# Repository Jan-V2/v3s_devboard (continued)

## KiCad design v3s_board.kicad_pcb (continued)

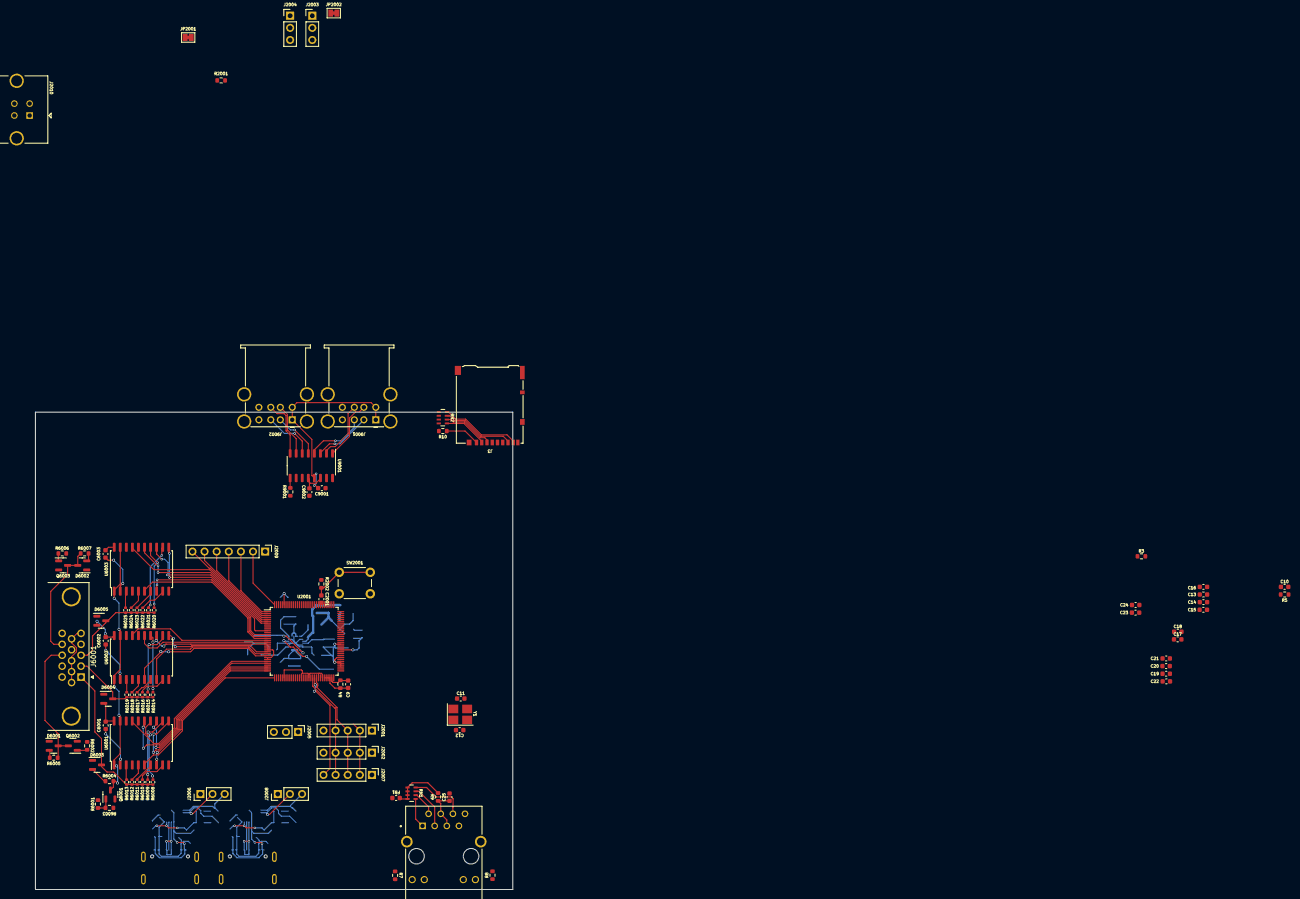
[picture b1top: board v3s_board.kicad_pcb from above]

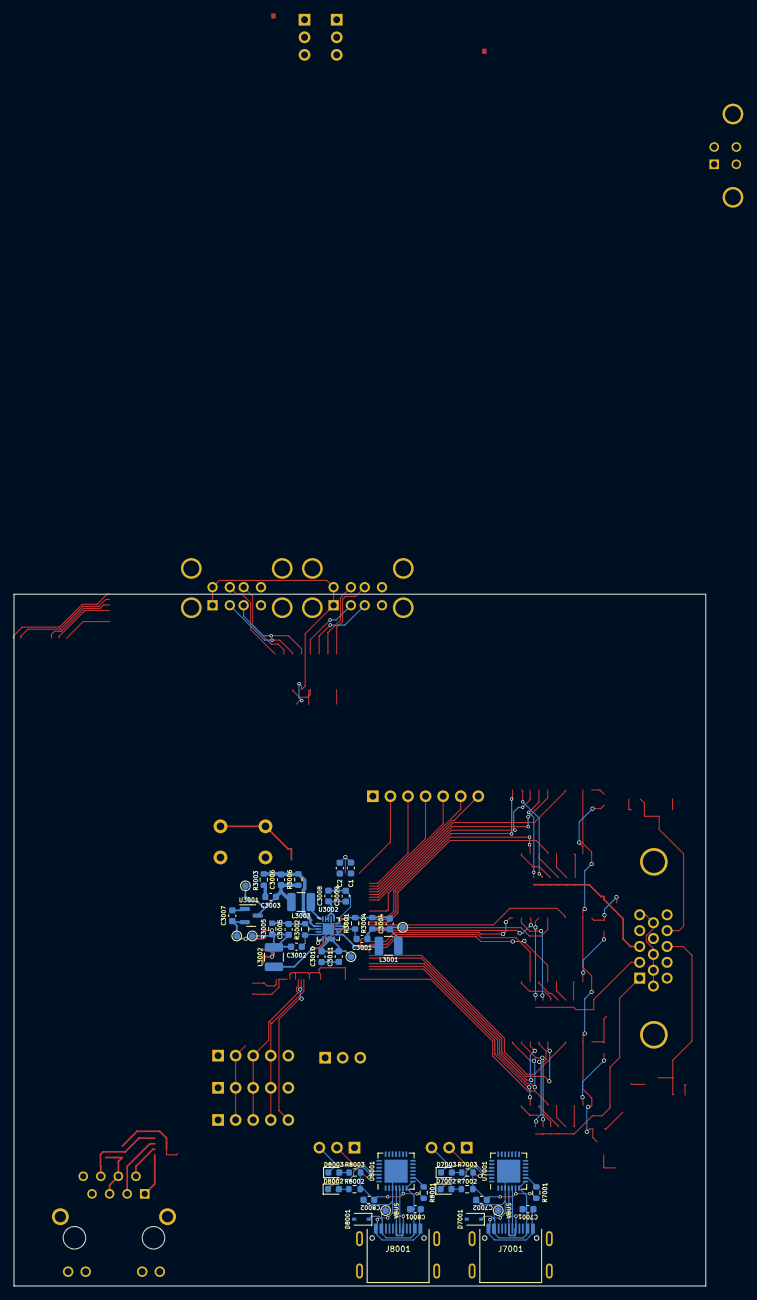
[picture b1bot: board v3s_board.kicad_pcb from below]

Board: 4 copper layers, 100.0 x 100.0 mm, 144 parts (51 on the bottom side), 134 nets.

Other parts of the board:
C7001, C7002: 100nf; C_0603_1608Metric
D7001: SD05_SOD323; D_SOD-323
D7002: LED YEL; LED_0603_1608Metric
D7003: LED RED; LED_0603_1608Metric
J7001: USB_C_Receptacle_USB2.0; TYPE-C-31-M-14_top_mnt_usb2
R7001: 10K; R_0603_1608Metric
R7002, R7003: 1K; R_0603_1608Metric
TP7001: VBUS; TestPoint_Pad_D1.0mm
U7001: CP2102N-Axx-xQFN28; QFN-28-1EP_5x5mm_P0.5mm_EP3.35x3.35mm

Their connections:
/v3s/UART0_RX: D7002.1 (K), U7001.26 (TXD); also elsewhere on the board
/v3s/UART0_TX: D7003.1 (K), U7001.25 (RXD); also elsewhere on the board
/v3s/cp2102_usb_to_uart/5V_USB: C7001.2, D7001.1 (A1), J7001.A4 (VBUS), J7001.A9 (VBUS), J7001.B4 (VBUS), J7001.B9 (VBUS), TP7001.1, U7001.7 (VREGIN), U7001.8 (VBUS)
/v3s/cp2102_usb_to_uart/vdd: C7002.1, R7001.1, R7002.1, R7003.1, U7001.6 (VDD)
GND: C7001.1, C7002.2, D7001.2 (A2), J7001.A1 (GND), J7001.A12 (GND), J7001.B1 (GND), J7001.B12 (GND), J7001.S1 (SHIELD), U7001.3 (GND), U7001.29 (GND); also elsewhere on the board
unnamed: D7002.2 (A), R7002.2
unnamed: D7003.2 (A), R7003.2
unnamed: J7001.A6 (D+), J7001.B6 (D+), U7001.4 (D+)
unnamed: J7001.A7 (D-), J7001.B7 (D-), U7001.5 (D-)
unnamed: R7001.2, U7001.9 (~RST)

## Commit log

2022-08-01 initial
2022-08-01 print
2022-10-16 almost done
2022-10-17 minor chantes
